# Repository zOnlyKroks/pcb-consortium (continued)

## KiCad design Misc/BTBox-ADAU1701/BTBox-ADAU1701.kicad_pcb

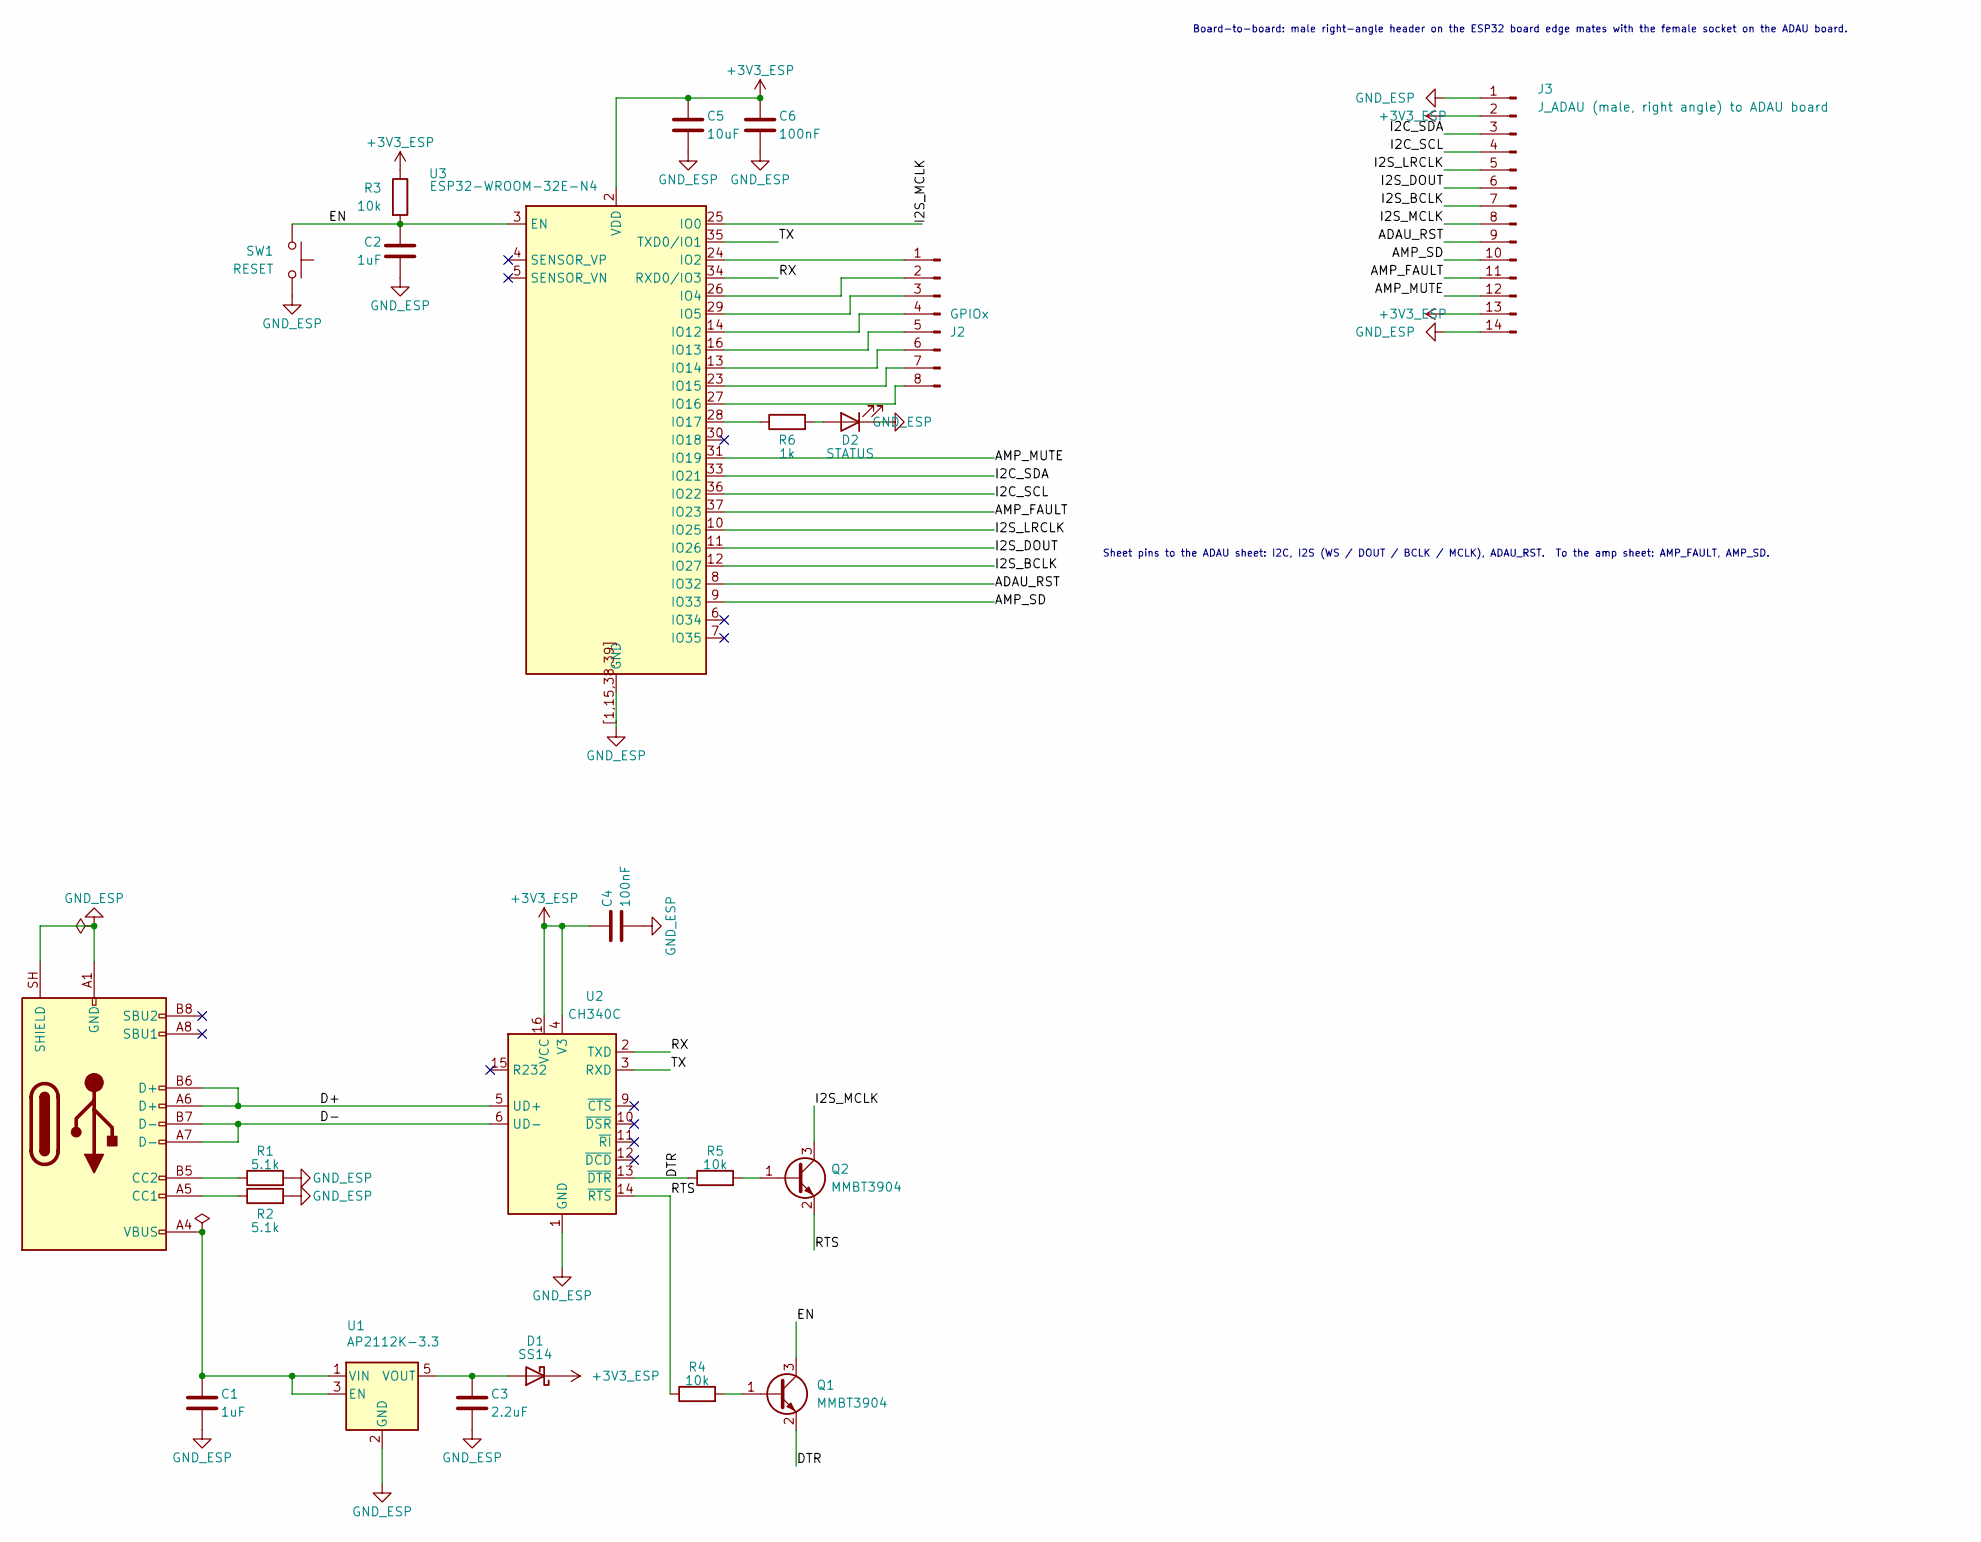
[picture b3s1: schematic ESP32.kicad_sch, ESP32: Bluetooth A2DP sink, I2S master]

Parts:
C1: 1uF; C_0805_2012Metric; LCSC Part # C28323
C2: 1uF; C_0603_1608Metric; LCSC Part # C15849
C3: 2.2uF; C_0805_2012Metric; LCSC Part # C19110
C4, C6: 100nF; C_0603_1608Metric; LCSC Part # C14663
C5: 10uF; C_0805_2012Metric; LCSC Part # C15850
D1: SS14; D_SMA; LCSC Part # C2480
D2: STATUS; LED_0603_1608Metric; LCSC Part # C2286
J1: USB-C (flash / console); USB_C_Receptacle_HRO_TYPE-C-31-M-12; LCSC Part # C165948
J2: GPIOx; PinSocket_1x08_P2.54mm_Vertical
J3: J_ADAU (male, right angle) to ADAU board; PinHeader_1x14_P2.54mm_Horizontal
Q1, Q2: MMBT3904; SOT-23; LCSC Part # C20526
R1, R2: 5.1k; R_0603_1608Metric; LCSC Part # C23186
R3, R4, R5: 10k; R_0603_1608Metric; LCSC Part # C25804
R6: 1k; R_0603_1608Metric; LCSC Part # C21190
SW1: RESET; SW_Push_1P1T_NO_CK_KMR2; LCSC Part # C72443
U1: AP2112K-3.3; SOT-23-5; LCSC Part # C51118
U2: CH340C; SOIC-16_3.9x9.9mm_P1.27mm; LCSC Part # C84681
U3: ESP32-WROOM-32E-N4; ESP32-WROOM-32E; LCSC Part # C701341

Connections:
+3V3_ESP: C4.1, C5.1, C6.1, D1.1 (K), J3.2, J3.13, R3.1, U2.4 (V3), U2.16 (VCC), U3.2 (VDD)
/ESP32/ADAU_RST: J3.9, U3.8 (IO32)
/ESP32/AMP_FAULT: J3.11, U3.37 (IO23)
/ESP32/AMP_MUTE: J3.12, U3.31 (IO19)
/ESP32/AMP_SD: J3.10, U3.9 (IO33)
/ESP32/D+: J1.A6 (D+), J1.B6 (D+), U2.5 (UD+)
/ESP32/D-: J1.A7 (D-), J1.B7 (D-), U2.6 (UD-)
/ESP32/DTR: Q1.2 (E), R5.1, U2.13 (~DTR)
/ESP32/EN: C2.1, Q1.3 (C), R3.2, SW1.1, U3.3 (EN)
/ESP32/I2C_SCL: J3.4, U3.36 (IO22)
/ESP32/I2C_SDA: J3.3, U3.33 (IO21)
/ESP32/I2S_BCLK: J3.7, U3.12 (IO27)
/ESP32/I2S_DOUT: J3.6, U3.11 (IO26)
/ESP32/I2S_LRCLK: J3.5, U3.10 (IO25)
/ESP32/I2S_MCLK: J3.8, Q2.3 (C), U3.25 (IO0)
/ESP32/RTS: Q2.2 (E), R4.1, U2.14 (~RTS)
/ESP32/RX: U2.2 (TXD), U3.34 (RXD0/IO3)
/ESP32/TX: U2.3 (RXD), U3.35 (TXD0/IO1)
GND_ESP: C1.2, C2.2, C3.2, C4.2, C5.2, C6.2, D2.1 (K), J1.A1 (GND), J1.A12 (GND), J1.B1 (GND), J1.B12 (GND), J1.SH (SHIELD), J3.1, J3.14, R1.2, R2.2, SW1.2, U1.2 (GND), U2.1 (GND), U3.1 (GND), U3.15 (GND), U3.38 (GND), U3.39 (GND), U3.[1,15,38,39] (GND)
unnamed: C3.1, D1.2 (A), U1.5 (VOUT)
unnamed: D2.2 (A), R6.2
unnamed: J1.A5 (CC1), R2.1
unnamed: J1.B5 (CC2), R1.1
unnamed: J2.1, U3.24 (IO2)
unnamed: J2.2, U3.26 (IO4)
unnamed: J2.3, U3.29 (IO5)
unnamed: J2.4, U3.14 (IO12)
unnamed: J2.5, U3.16 (IO13)
unnamed: J2.6, U3.13 (IO14)
unnamed: J2.7, U3.23 (IO15)
unnamed: J2.8, U3.27 (IO16)
unnamed: Q1.1 (B), R4.2
unnamed: Q2.1 (B), R5.2
unnamed: C1.1, J1.A4 (VBUS), J1.A9 (VBUS), J1.B4 (VBUS), J1.B9 (VBUS), U1.1 (VIN), U1.3 (EN)
unnamed: R6.1, U3.28 (IO17)

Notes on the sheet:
Board-to-board: male right-angle header on the ESP32 board edge mates with the female socket on the ADAU board.
Sheet pins to the ADAU sheet: I2C, I2S (WS / DOUT / BCLK / MCLK), ADAU_RST. To the amp sheet: AMP_FAULT, AMP_SD.

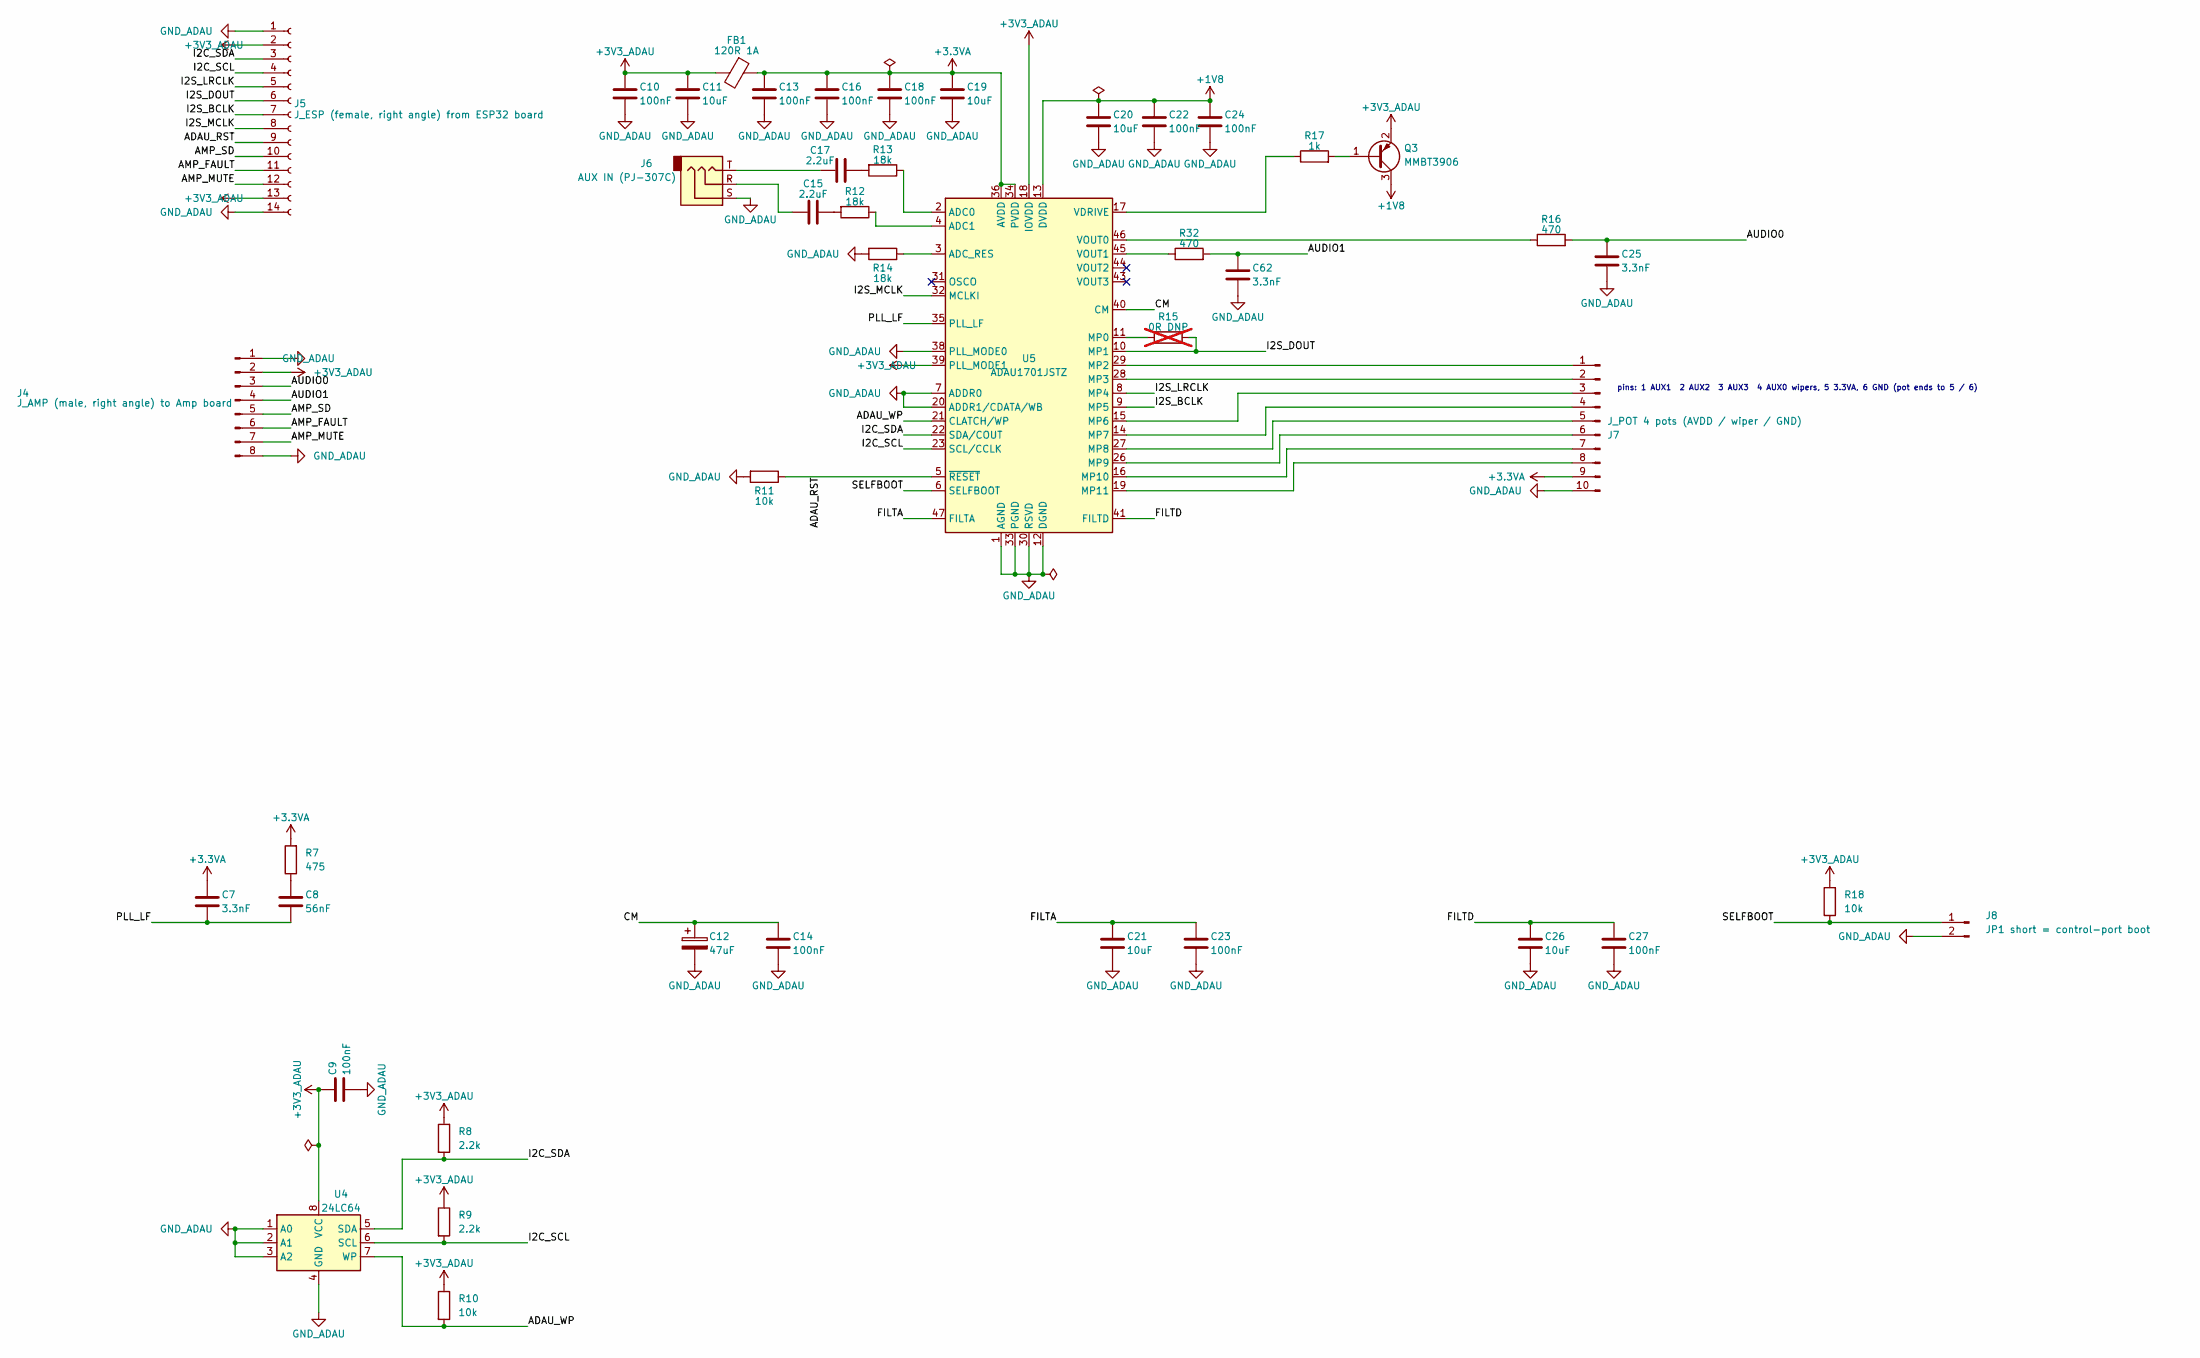
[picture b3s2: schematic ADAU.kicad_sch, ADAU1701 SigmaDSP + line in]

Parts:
C7, C25: 3.3nF; C_0603_1608Metric; LCSC Part # C1613
C8: 56nF; C_0603_1608Metric; LCSC Part # C282072
C9, C10, C13, C14, C16, C18, C22, C23, C24, C27: 100nF; C_0603_1608Metric; LCSC Part # C14663
C11, C19, C20, C21, C26: 10uF; C_0805_2012Metric; LCSC Part # C15850
C12: 47uF; CP_Elec_6.3x5.4; LCSC Part # C7469965
C15, C17: 2.2uF; C_0805_2012Metric; LCSC Part # C19110
C62: 3.3nF; C_0603_1608Metric
FB1: 120R 1A; L_0805_2012Metric; LCSC Part # C356986
J4: J_AMP (male, right angle) to Amp board; PinHeader_1x08_P2.54mm_Horizontal
J5: J_ESP (female, right angle) from ESP32 board; PinSocket_1x14_P2.54mm_Horizontal
J6: AUX IN (PJ-307C); AUDIO-TH_PJ307C; LCSC Part # C16684
J7: J_POT 4 pots (AVDD / wiper / GND); PinSocket_1x10_P2.54mm_Vertical
J8: JP1 short = control-port boot; PinHeader_1x02_P2.54mm_Vertical; LCSC Part # C2894925
Q3: MMBT3906; SOT-23; LCSC Part # C53444
R7: 475; R_0603_1608Metric; LCSC Part # C23181
R8, R9: 2.2k; R_0603_1608Metric; LCSC Part # C4190
R10, R11, R18: 10k; R_0603_1608Metric; LCSC Part # C25804
R12, R13, R14: 18k; R_0603_1608Metric; LCSC Part # C100821
R15: 0R DNP; R_0603_1608Metric; LCSC Part # C21189; not fitted
R16: 470; R_0603_1608Metric; LCSC Part # C23179
R17: 1k; R_0603_1608Metric; LCSC Part # C21190
R32: 470; R_0603_1608Metric
U4: 24LC64; SOIC-8_3.9x4.9mm_P1.27mm; LCSC Part # C5460
U5: ADAU1701JSTZ; LQFP-48_7x7mm_P0.5mm; LCSC Part # C3001875

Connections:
+1V8: C20.1, C22.1, C24.1, Q3.3 (C), U5.13 (DVDD), U5.24 (DVDD)
+3.3VA: C7.2, C13.1, C16.1, C18.1, C19.1, FB1.1, J7.9, R7.2, U5.34 (PVDD), U5.36 (AVDD), U5.48 (AVDD)
+3V3_ADAU: C9.1, C10.1, C11.1, FB1.2, J4.2, J5.2, J5.13, Q3.2 (E), R8.1, R9.1, R10.1, R18.2, U4.8 (VCC), U5.18 (IOVDD), U5.39 (PLL_MODE1)
/ADAU/ADAU_RST: J5.9, R11.1, U5.5 (~RESET)
/ADAU/ADAU_WP: R10.2, U4.7 (WP), U5.21 (CLATCH/WP)
/ADAU/AMP_FAULT: J4.6, J5.11
/ADAU/AMP_MUTE: J4.7, J5.12
/ADAU/AMP_SD: J4.5, J5.10
/ADAU/AUDIO0: C25.1, J4.3, R16.2
/ADAU/AUDIO1: C62.1, J4.4, R32.2
/ADAU/CM: C12.1, C14.1, U5.40 (CM)
/ADAU/FILTA: C21.1, C23.1, U5.47 (FILTA)
/ADAU/FILTD: C26.1, C27.1, U5.41 (FILTD)
/ADAU/I2C_SCL: J5.4, R9.2, U4.6 (SCL), U5.23 (SCL/CCLK)
/ADAU/I2C_SDA: J5.3, R8.2, U4.5 (SDA), U5.22 (SDA/COUT)
/ADAU/I2S_BCLK: J5.7, U5.9 (MP5)
/ADAU/I2S_DOUT: J5.6, R15.2, U5.10 (MP1)
/ADAU/I2S_LRCLK: J5.5, U5.8 (MP4)
/ADAU/I2S_MCLK: J5.8, U5.32 (MCLKI)
/ADAU/PLL_LF: C7.1, C8.1, U5.35 (PLL_LF)
/ADAU/SELFBOOT: J8.1, R18.1, U5.6 (SELFBOOT)
GND_ADAU: C9.2, C10.2, C11.2, C12.2, C13.2, C14.2, C16.2, C18.2, C19.2, C20.2, C21.2, C22.2, C23.2, C24.2, C25.2, C26.2, C27.2, C62.2, J4.1, J4.8, J5.1, J5.14, J6.S, J7.10, J8.2, R11.2, R14.2, U4.1 (A0), U4.2 (A1), U4.3 (A2), U4.4 (GND), U5.1 (AGND), U5.7 (ADDR0), U5.12 (DGND), U5.20 (ADDR1/CDATA/WB), U5.25 (DGND), U5.30 (RSVD), U5.33 (PGND), U5.37 (AGND), U5.38 (PLL_MODE0), U5.42 (AGND)
unnamed: C8.2, R7.1
unnamed: C15.1, R12.2
unnamed: C15.2, J6.R
unnamed: C17.1, R13.2
unnamed: C17.2, J6.T
unnamed: J7.1, U5.29 (MP2)
unnamed: J7.2, U5.28 (MP3)
unnamed: J7.3, U5.15 (MP6)
unnamed: J7.4, U5.14 (MP7)
unnamed: J7.5, U5.27 (MP8)
unnamed: J7.6, U5.26 (MP9)
unnamed: J7.7, U5.16 (MP10)
unnamed: J7.8, U5.19 (MP11)
unnamed: Q3.1 (B), R17.2
unnamed: R13.1, U5.2 (ADC0)
unnamed: R12.1, U5.4 (ADC1)
unnamed: R14.1, U5.3 (ADC_RES)
unnamed: R15.1, U5.11 (MP0)
unnamed: R17.1, U5.17 (VDRIVE)
unnamed: R16.1, U5.46 (VOUT0)
unnamed: R32.1, U5.45 (VOUT1)

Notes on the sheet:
pins: 1 AUX1 2 AUX2 3 AUX3 4 AUX0 wipers, 5 3.3VA, 6 GND (pot ends to 5 / 6)

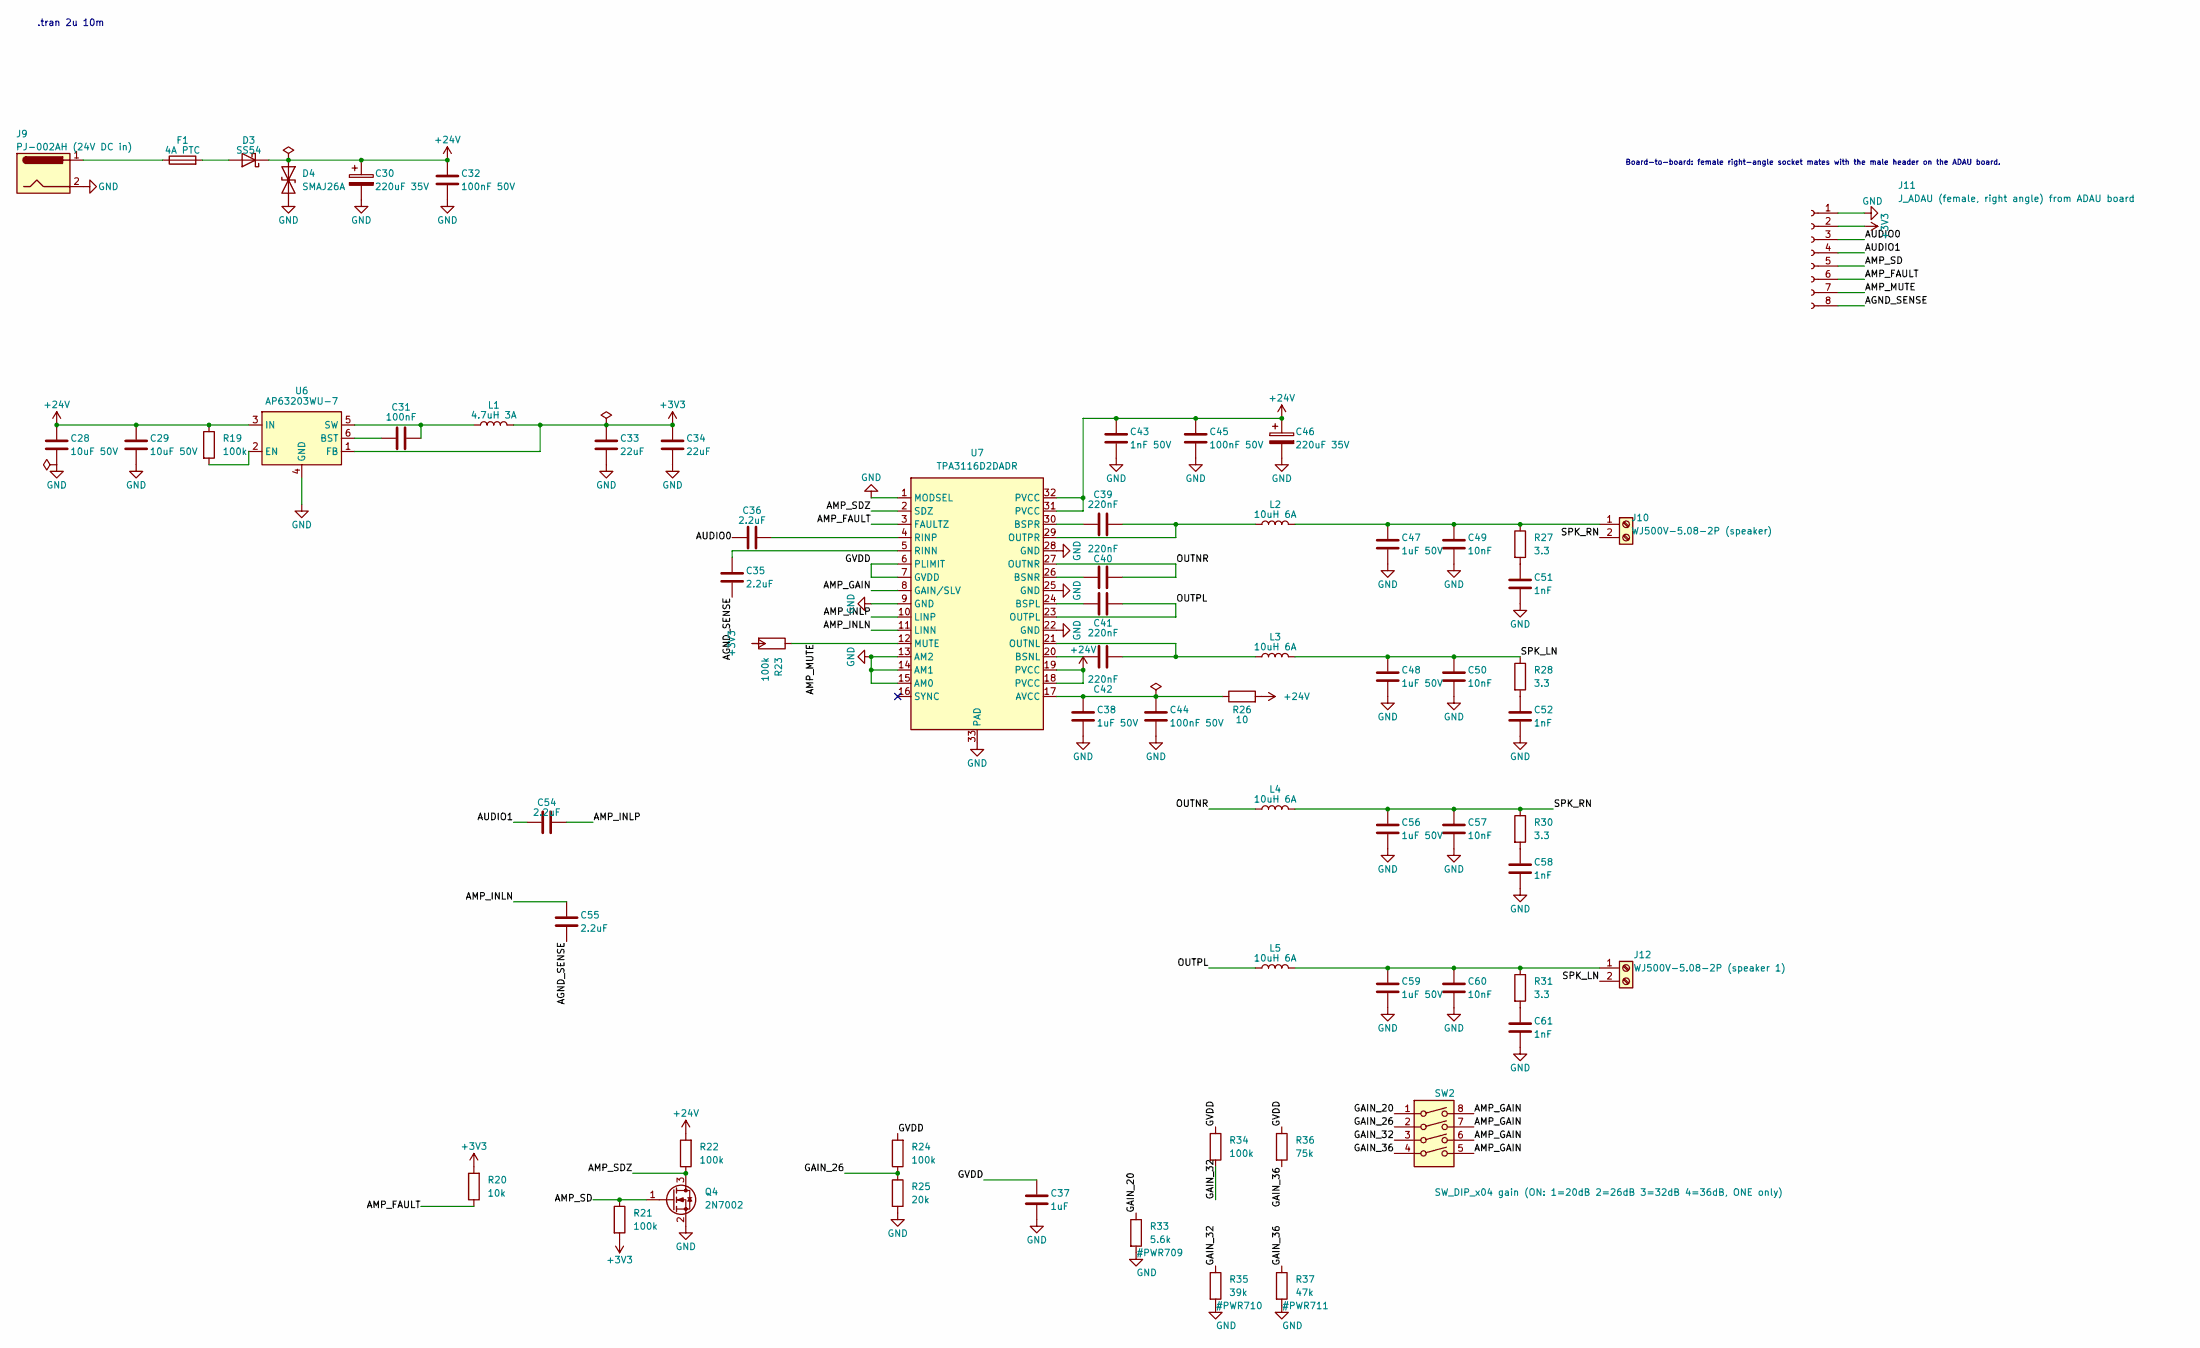
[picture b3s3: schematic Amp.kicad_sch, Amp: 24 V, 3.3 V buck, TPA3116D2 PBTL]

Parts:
C28, C29: 10uF 50V; C_1206_3216Metric; LCSC Part # C13585
C30, C46: 220uF 35V; CP_Elec_10x10.5; LCSC Part # C2886113
C31: 100nF; C_0603_1608Metric; LCSC Part # C14663
C32, C44, C45: 100nF 50V; C_0805_2012Metric; LCSC Part # C49678
C33, C34: 22uF; C_0805_2012Metric; LCSC Part # C45783
C35, C36: 2.2uF; C_0805_2012Metric; LCSC Part # C19110
C37: 1uF; C_0805_2012Metric; LCSC Part # C28323
C38, C47, C48: 1uF 50V; C_0805_2012Metric; LCSC Part # C91185
C39, C40, C41, C42: 220nF; C_0603_1608Metric; LCSC Part # C64705
C43: 1nF 50V; C_0603_1608Metric; LCSC Part # C1588
C49, C50: 10nF; C_0603_1608Metric; LCSC Part # C57112
C51, C52: 1nF; C_0603_1608Metric; LCSC Part # C1588
C54, C55: 2.2uF; C_0805_2012Metric
C56, C59: 1uF 50V; C_0805_2012Metric
C57, C60: 10nF; C_0603_1608Metric
C58, C61: 1nF; C_0603_1608Metric
D3: SS54; D_SMA; LCSC Part # C22452
D4: SMAJ26A; D_SMA; LCSC Part # C148225
F1: 4A PTC; Fuse_1812_4532Metric
J9: PJ-002AH (24V DC in); BarrelJack_CUI_PJ-002AH; LCSC Part # C2961147
J10: WJ500V-5.08-2P (speaker); TerminalBlock_Phoenix_MKDS-1,5-2-5.08_1x02_P5.08mm_Horizont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; LCSC Part # C8465
J11: J_ADAU (female, right angle) from ADAU board; PinSocket_1x08_P2.54mm_Horizontal
J12: WJ500V-5.08-2P (speaker 1); TerminalBlock_Phoenix_MKDS-1,5-2-5.08_1x02_P5.08mm_Horizont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; LCSC Part # C8465
L1: 4.7uH 3A; L_Bourns-SRN6028; LCSC Part # C168028
L2, L3: 10uH 6A; L_12x12mm_H8mm; LCSC Part # C2041557
L4, L5: 10uH 6A; L_12x12mm_H8mm
Q4: 2N7002; SOT-23; LCSC Part # C8545
R19, R21, R22, R23, R24: 100k; R_0603_1608Metric; LCSC Part # C25803
R20: 10k; R_0603_1608Metric; LCSC Part # C25804
R25: 20k; R_0603_1608Metric; LCSC Part # C4184
R26: 10; R_0603_1608Metric; LCSC Part # C22859
R27, R28, R30, R31: 3.3; R_0603_1608Metric
R33: 5.6k; R_0603_1608Metric
R34: 100k; R_0603_1608Metric
R35: 39k; R_0603_1608Metric
R36: 75k; R_0603_1608Metric
R37: 47k; R_0603_1608Metric
SW2: SW_DIP_x04 gain (ON: 1=20dB 2=26dB 3=32dB 4=36dB,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; SW_DIP_SPSTx04_Slide_6.7x11.72mm_W8.61mm_P2.54mm_LowProfile
U6: AP63203WU-7; TSOT-23-6; LCSC Part # C780769
U7: TPA3116D2DADR; HTSSOP-32_L11.0-W6.1-P0.65-LS8.1-BL; LCSC Part # C50144

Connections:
+3V3: C33.1, C34.1, J11.2, L1.2, R20.2, R21.2, R23.2, U6.1 (FB)
+24V: C28.1, C29.1, C30.1, C32.1, C43.1, C45.1, C46.1, D3.1 (K), D4.1 (A1), R19.1, R22.2, R26.2, U6.3 (IN), U7.18 (PVCC), U7.19 (PVCC), U7.31 (PVCC), U7.32 (PVCC)
/Amp/AGND_SENSE: C35.2, C55.2, J11.8
/Amp/AMP_FAULT: J11.6, R20.1, U7.3 (FAULTZ)
/Amp/AMP_GAIN: SW2.5, SW2.6, SW2.7, SW2.8, U7.8 (GAIN/SLV)
/Amp/AMP_INLN: C55.1, U7.11 (LINN)
/Amp/AMP_INLP: C54.2, U7.10 (LINP)
/Amp/AMP_MUTE: J11.7, R23.1, U7.12 (MUTE)
/Amp/AMP_SD: J11.5, Q4.1 (G), R21.1
/Amp/AMP_SDZ: Q4.3 (D), R22.1, U7.2 (SDZ)
/Amp/AUDIO0: C36.1, J11.3
/Amp/AUDIO1: C54.1, J11.4
/Amp/GAIN_20: R33.1, SW2.1
/Amp/GAIN_26: R24.1, R25.1, SW2.2
/Amp/GAIN_32: R34.2, R35.1, SW2.3
/Amp/GAIN_36: R36.2, R37.1, SW2.4
/Amp/GVDD: C37.1, R24.2, R34.1, R36.1, U7.6 (PLIMIT), U7.7 (GVDD)
/Amp/OUTNR: C40.1, L4.1, U7.27 (OUTNR)
/Amp/OUTPL: C41.2, L5.1, U7.23 (OUTPL)
/Amp/SPK_LN: C48.1, C50.1, J12.2, L3.2, R28.1
/Amp/SPK_RN: C56.1, C57.1, J10.2, L4.2, R30.1
GND: C28.2, C29.2, C30.2, C32.2, C33.2, C34.2, C37.2, C38.2, C43.2, C44.2, C45.2, C46.2, C47.2, C48.2, C49.2, C50.2, C51.2, C52.2, C56.2, C57.2, C58.2, C59.2, C60.2, C61.2, D4.2 (A2), J9.2, J11.1, Q4.2 (S), R25.2, R33.2, R35.2, R37.2, U6.4 (GND), U7.1 (MODSEL), U7.9 (GND), U7.13 (AM2), U7.14 (AM1), U7.15 (AM0), U7.22 (GND), U7.25 (GND), U7.28 (GND), U7.33 (PAD)
unnamed: C51.1, R27.2
unnamed: C52.1, R28.2
unnamed: C58.1, R30.2
unnamed: C61.1, R31.2
unnamed: D3.2 (A), F1.2
unnamed: F1.1, J9.1
unnamed: C47.1, C49.1, J10.1, L2.2, R27.1
unnamed: C59.1, C60.1, J12.1, L5.2, R31.1
unnamed: C31.1, U6.6 (BST)
unnamed: R19.2, U6.2 (EN)
unnamed: C31.2, L1.1, U6.5 (SW)
unnamed: C38.1, C44.1, R26.1, U7.17 (AVCC)
unnamed: C42.2, U7.20 (BSNL)
unnamed: C40.2, U7.26 (BSNR)
unnamed: C41.1, U7.24 (BSPL)
unnamed: C39.1, U7.30 (BSPR)
unnamed: C42.1, L3.1, U7.21 (OUTNL)
unnamed: C39.2, L2.1, U7.29 (OUTPR)
unnamed: C35.1, U7.5 (RINN)
unnamed: C36.2, U7.4 (RINP)

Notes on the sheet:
.tran 2u 10m
Board-to-board: female right-angle socket mates with the male header on the ADAU board.

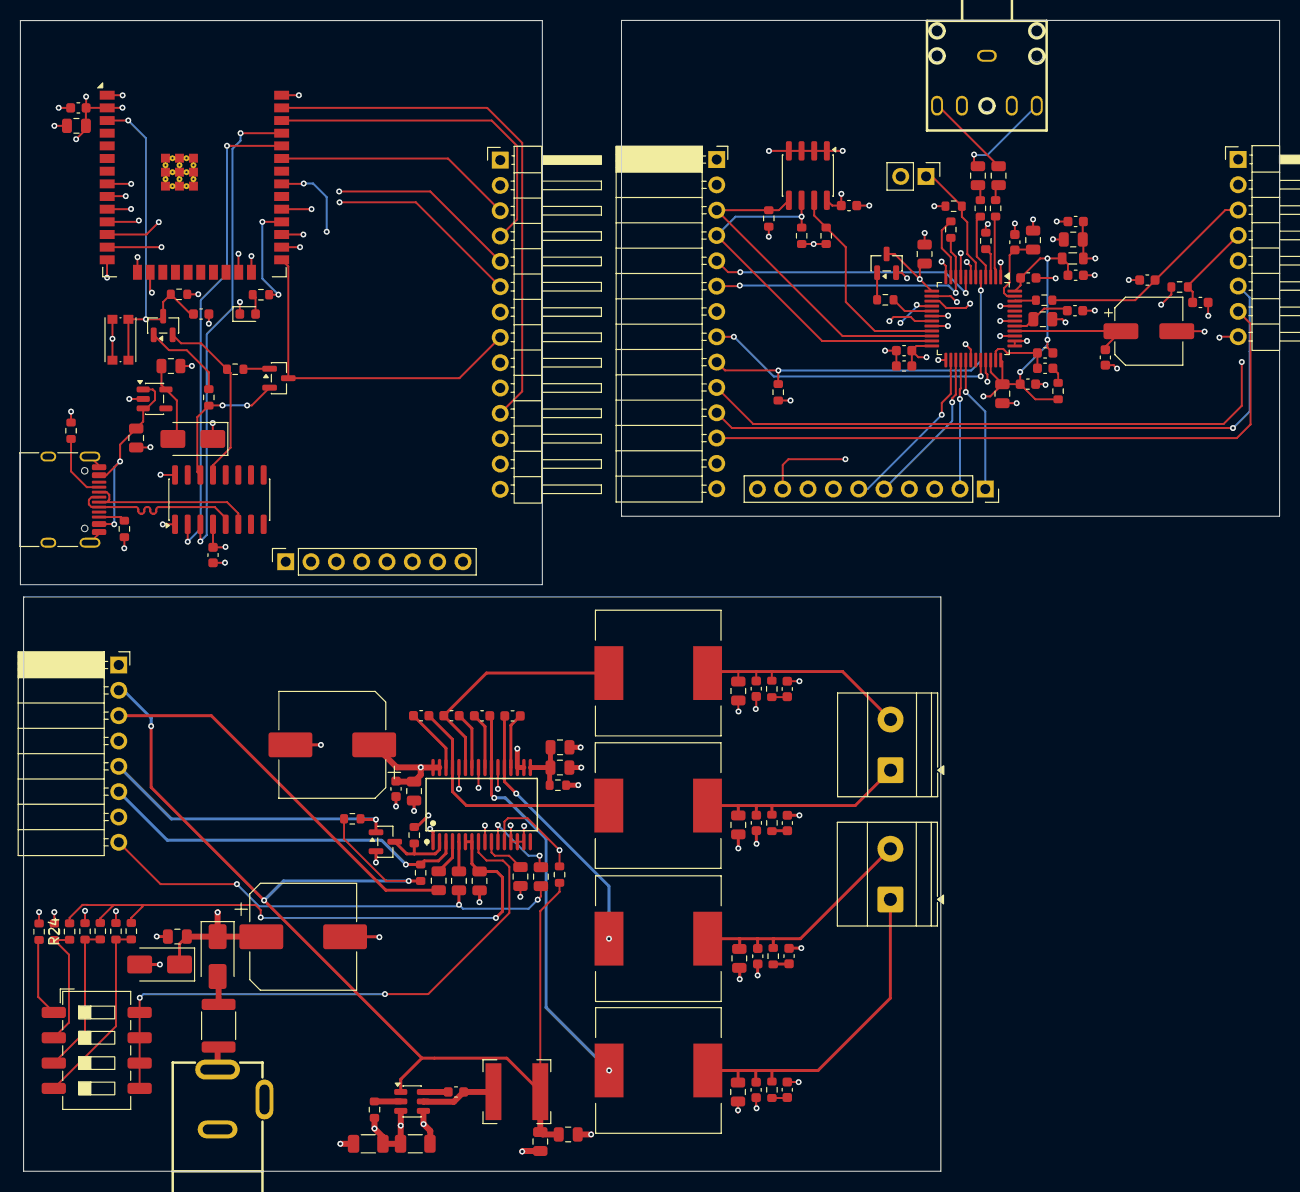
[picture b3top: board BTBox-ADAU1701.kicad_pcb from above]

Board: 4 copper layers, 126.3 x 115.4 mm, 133 parts (0 on the bottom side), 120 nets.

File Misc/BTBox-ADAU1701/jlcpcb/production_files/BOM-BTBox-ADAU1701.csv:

Comment,Designator,Footprint,LCSC,Quantity
10,R26,R_0603_1608Metric,C22859,1
100k,"R19,R21,R22,R23,R24",R_0603_1608Metric,C25803,5
100nF,"C10,C13,C14,C16,C18,C22,C23,C24,C27,C31,C4,C6,C9",C_0603_1608Metric,C14663,13
100nF 50V,"C32,C44,C45",C_0805_2012Metric,C49678,3
10k,"R10,R11,R18,R20,R3,R4,R5",R_0603_1608Metric,C25804,7
10nF,"C49,C50",C_0603_1608Metric,C57112,2
10uF,"C11,C19,C20,C21,C26,C5",C_0805_2012Metric,C15850,6
10uF 50V,"C28,C29",C_1206_3216Metric,C13585,2
10uH 6A,"L2,L3",L_12x12mm_H8mm,C2041557,2
120R 1A,FB1,L_0805_2012Metric,C88990,1
18k,"R12,R13,R14",R_0603_1608Metric,C25810,3
1k,"R17,R6",R_0603_1608Metric,C21190,2
1nF,"C51,C52",C_0603_1608Metric,C1588,2
1nF 50V,C43,C_0603_1608Metric,C1588,1
1uF,C2,C_0603_1608Metric,C15849,1
1uF,"C1,C37",C_0805_2012Metric,C28323,2
1uF 50V,"C38,C47,C48",C_0805_2012Metric,C28323,3
2.2k,"R8,R9",R_0603_1608Metric,C4190,2
2.2uF,"C15,C17,C3,C35,C36",C_0805_2012Metric,C377773,5
20k,R25,R_0603_1608Metric,C4184,1
220nF,"C39,C40,C41,C42",C_0603_1608Metric,C21120,4
220uF 35V,"C30,C46",CP_Elec_10x10.5,C48970715,2
22uF,"C33,C34",C_0805_2012Metric,C45783,2
24LC64,U4,SOIC-8_3.9x4.9mm_P1.27mm,C5460,1
2N7002,Q4,SOT-23,C8545,1
3.3,"R27,R28",R_0603_1608Metric,C22979,2
3.3nF,"C25,C7",C_0603_1608Metric,C1613,2
4.7uH 3A,L1,L_Bourns-SRN6028,C168028,1
470,R16,R_0603_1608Metric,C23179,1
475,R7,R_0603_1608Metric,C23181,1
47uF,C12,CP_Elec_6.3x5.4,C52164971,1
4A PTC,F1,Fuse_1812_4532Metric,C2982282,1
5.1k,"R1,R2",R_0603_1608Metric,C23186,2
56nF,C8,C_0603_1608Metric,C282072,1
ADAU1701JSTZ,U5,LQFP-48_7x7mm_P0.5mm,C3001875,1
AP2112K-3.3,U1,SOT-23-5,C51118,1
AP63203WU-7,U6,TSOT-23-6,C780769,1
AUX IN (PJ-307C),J3,AUDIO-TH_PJ307C,C16684,1
CH340C,U2,SOIC-16_3.9x9.9mm_P1.27mm,C84681,1
ESP32-WROOM-32E-N4,U3,ESP32-WROOM-32E,C701341,1
JP1 short = control-port boot,J5,PinHeader_1x02_P2.54mm_Vertical,C2894925,1
J_POT 4 pots (AVDD / wiper / GND),J4,PinHeader_1x06_P2.54mm_Vertical,C37208,1
J_UI buttons,J2,PinHeader_1x04_P2.54mm_Vertical,C2691448,1
MMBT3904,"Q1,Q2",SOT-23,C20526,2
MMBT3906,Q3,SOT-23,C7420354,1
PJ-002AH (24V DC in),J6,BarrelJack_CUI_PJ-002AH,C2961147,1
RESET,SW1,SW_Push_1P1T_NO_CK_KMR2,C72443,1
SMAJ26A,D4,D_SMA,C19077543,1
SS14,D1,D_SMA,C2480,1
SS54,D3,D_SMA,C22452,1
STATUS,D2,LED_0603_1608Metric,C2286,1
TPA3116D2DADR,U7,HTSSOP-32_L11.0-W6.1-P0.65-LS8.1-BL,C50144,1
USB-C (flash / console),J1,USB_C_Receptacle_HRO_TYPE-C-31-M-12,C165948,1
WJ500V-5.08-2P (speaker),J7,"TerminalBlock_Phoenix_MKDS-1,5-2-5.08_1x02_P5.08mm_Horizontal",C8465,1

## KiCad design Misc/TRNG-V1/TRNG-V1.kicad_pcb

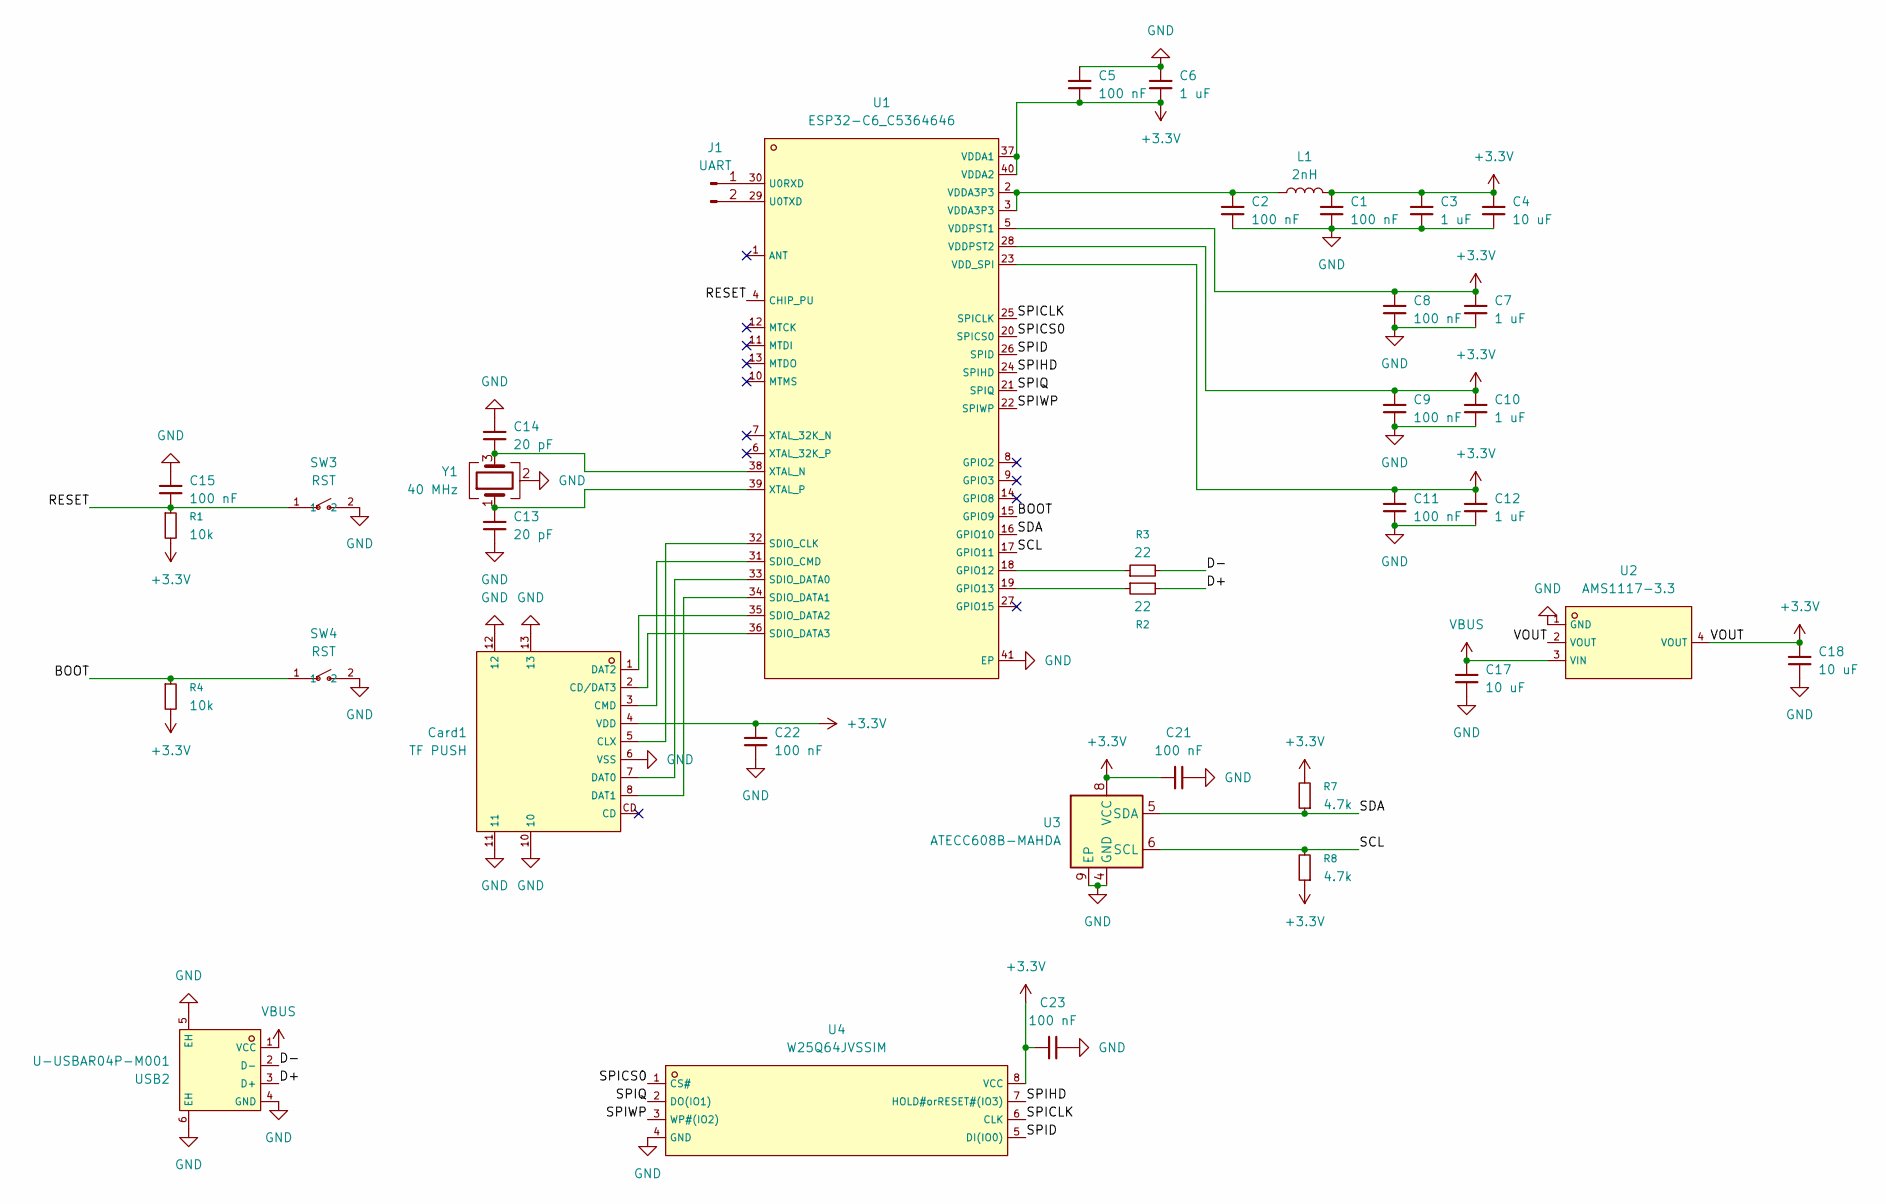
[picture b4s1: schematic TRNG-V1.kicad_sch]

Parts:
C1, C2, C5, C8, C9, C11, C15, C21, C22, C23: 100 nF; C_0603_1608Metric
C3, C6, C7, C10, C12: 1 uF; C_0603_1608Metric
C4, C17, C18: 10 uF; C_0603_1608Metric
C13, C14: 20 pF; C_0603_1608Metric
Card1: TF PUSH; C393941_TF-SMD_TF-PUSH; LCSC C393941
J1: UART; PinHeader_1x02_P2.54mm_Vertical
L1: 2nH; L_0805_2012Metric
R1, R4: 10k; R_0603_1608Metric
R2, R3: 22; R_0603_1608Metric
R7, R8: 4.7k; R_0603_1608Metric
SW3, SW4: RST; C54407262_SW-SMD_L4_0-W3_0-LS5_0; LCSC C54407262
U1: ESP32-C6_C5364646; C5364646_QFN-40_L5_0-W5_0-P0_40-TL-EP3_3; LCSC C5364646
U2: AMS1117-3.3; C6186_SOT-223-3_L6_5-W3_4-P2_30-LS7_0-BR; LCSC C6186
U3: ATECC608B-MAHDA; DFN-8-1EP_3x2mm_P0.5mm_EP1.3x1.5mm
U4: W25Q64JVSSIM; C5362615_SOIC-8_L5_2-W5_2-P1_27-LS8_0-BL; LCSC C5362615
USB2: U-USBAR04P-M001; C386752_USB-SMD_KH-USB-AM-4P-CB; LCSC C386752
Y1: 40 MHz; Crystal_SMD_3225-4Pin_3.2x2.5mm

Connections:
+3.3V: C1.1, C3.1, C4.1, C5.2, C6.2, C7.1, C8.1, C9.1, C10.1, C11.1, C12.1, C18.1, C21.1, C22.2, C23.1, Card1.4 (VDD), L1.2, R1.2, R4.2, R7.2, R8.1, U1.5 (VDDPST1), U1.23 (VDD_SPI), U1.28 (VDDPST2), U1.37 (VDDA1), U1.40 (VDDA2), U2.2 (VOUT), U2.4 (VOUT), U3.8 (VCC), U4.8 (VCC)
/BOOT: R4.1, SW4.1, U1.15 (GPIO9)
/D+: R2.2, USB2.3 (D+)
/D-: R3.2, USB2.2 (D-)
/RESET: C15.2, R1.1, SW3.1, U1.4 (CHIP_PU)
/SCL: R8.2, U1.17 (GPIO11), U3.6 (SCL)
/SDA: R7.1, U1.16 (GPIO10), U3.5 (SDA)
/SPICLK: U1.25 (SPICLK), U4.6 (CLK)
/SPICS0: U1.20 (SPICS0), U4.1 (CS#)
/SPID: U1.26 (SPID), U4.5 (DI(IO0))
/SPIHD: U1.24 (SPIHD), U4.7 (HOLD#orRESET#(IO3))
/SPIQ: U1.21 (SPIQ), U4.2 (DO(IO1))
/SPIWP: U1.22 (SPIWP), U4.3 (WP#(IO2))
GND: C1.2, C2.2, C3.2, C4.2, C5.1, C6.1, C7.2, C8.2, C9.2, C10.2, C11.2, C12.2, C13.2, C14.1, C15.1, C17.2, C18.2, C21.2, C22.1, C23.2, Card1.6 (VSS), Card1.10, Card1.11, Card1.12, Card1.13, SW3.2, SW4.2, U1.41 (EP), U2.1 (GND), U3.4 (GND), U3.9 (EP), U4.4 (GND), USB2.4 (GND), USB2.5 (EH), USB2.6 (EH), Y1.2 (G), Y1.4 (G)
unnamed: C2.1, L1.1, U1.2 (VDDA3P3), U1.3 (VDDA3P3)
unnamed: Card1.2 (CD/DAT3), U1.36 (SDIO_DATA3)
unnamed: Card1.5 (CLX), U1.32 (SDIO_CLK)
unnamed: Card1.3 (CMD), U1.31 (SDIO_CMD)
unnamed: Card1.7 (DAT0), U1.33 (SDIO_DATA0)
unnamed: Card1.8 (DAT1), U1.34 (SDIO_DATA1)
unnamed: Card1.1 (DAT2), U1.35 (SDIO_DATA2)
unnamed: J1.1, U1.30 (U0RXD)
unnamed: J1.2, U1.29 (U0TXD)
unnamed: R3.1, U1.18 (GPIO12)
unnamed: R2.1, U1.19 (GPIO13)
unnamed: C14.2, U1.38 (XTAL_N), Y1.3
unnamed: C13.1, U1.39 (XTAL_P), Y1.1
VBUS: C17.1, U2.3 (VIN), USB2.1 (VCC)

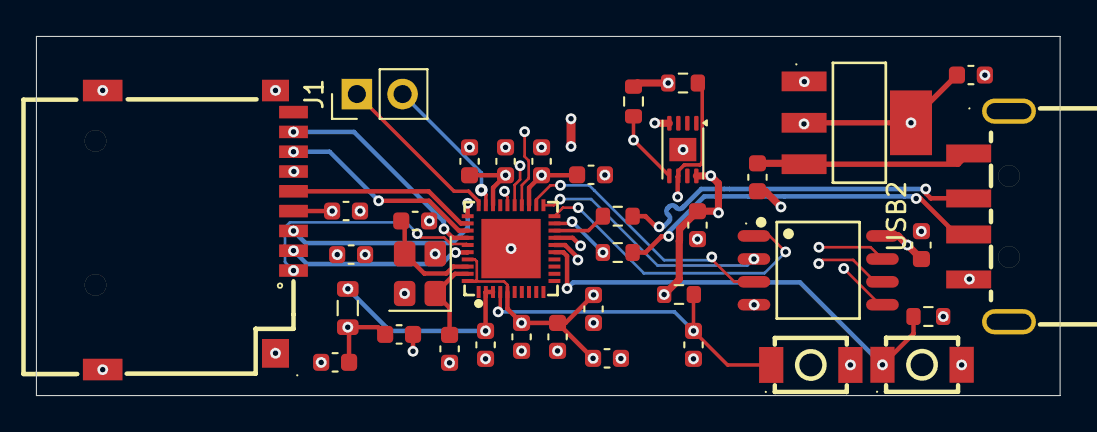
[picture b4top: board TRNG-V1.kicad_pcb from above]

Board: 4 copper layers, 56.9 x 20.0 mm, 37 parts (0 on the bottom side), 28 nets.
